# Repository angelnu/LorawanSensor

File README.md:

# STM32 Low Power LoraWan Sensors

This project provides a framework to easily build LoraWan devices. The requirements are:
- sensors that could run without replacing batteries during the life cycle of the device
- small size
- easy to build and program (need a 20-30)
- simple to create a new type: just a new file
- cost bellow 20€
- resist the outside weather with easy to 3D print cages

The sensor can work on a CR123 battery for 20 years (self-discharge of the battery being the main factor). It sends the battery voltage and (optionally) the temp of the MCU (using factory calibration).

For each new detected device it generates unique LoraWan keys and upload them to flash. This way the same firmware can be used for multiple instances of the same board.

**NOTE**: Do not put the config directory in a public repository. Instead save as extra home/private repository so you have versioning while keeping your keys private!

Download commands might be used to query or modify the configuration. See the commands section bellow.

## Bill of Materials
Devices can be built for ca 10-20€ ussing the following parts:
- STM32 MCU - any of the following:
  - STM32L412KB (3 €) - prefered: 128KB RAM for a future firmware OTA update
    - STM32L412KBT6 128K Flash,  8K RAM, LQFP-32
  - STM32L412K8 (2.5 €) - same as STM32L412KB but only 64K Flash
    - STM32L412K8T6 64K Flash,  8K RAM, LQFP-32
  - STM32L010K8 (1.5 €) - cheaper MCO+, slower, less memory, not tem and slightly higher consumption
    - STM32L412K8T6 64K Flash,  8K RAM, LQFP-32 
- RFM95W (3.5 € via Aliexpress, 3x this price if bought in Europe)
- RC123a battery and holder (2€ via Aliexpress, 2x this price if bought in Europe)
- PCB (2-5 € when ordering 12 from [Aisler](https://aisler.net) ) - see [Devices](devices) folder for the sources and the uploaded PCBs to [Aisler](https://aisler.net)
- 3D-printed boxes - see cages in [Devices](devices) folder
- some SMT components (1 €) - see schematics in [Devices](devices) folder

## Downlink commands

Downlink commands are used to query and/or modify the device settings without having to reprogram the flash. Each command uses one byte plus optional data depending on the command. The commands are implemtented in the `lorawan_process_command` at [lorawan.cpp](src/lorawan.cpp#L188)

Commands will be queued and transferred to the device after the next uplink transfer. Multiple commands can be queued but be carefull not to exceed to the watdown timeout or the device will get reset.

Commands:
- 0x00 - READ configuration
  - Description: Returns the configuration of the device. See [device_config_t](src/config.h#L23) for more details on the struct
  - Additional downlink bytes: none
  - Example output: 02 03 3C00 05 3C 6400 5802 01 0A 05 FF
- 0x01 - Reset config to the default
  - Additional downlink bytes: none
- 0x02 - Sets the configuration
  - Additional downlink bytes: config as returned by the 0x00 command
  - Example input: 02 02033C00053C64005802010A05FF
- 0x05 - Read Device UID
  - Additional downlink bytes: none
  - Output: 12 bytes with STM32 UID
- 0x06 - Read firmware GIT commit
  - Additional downlink bytes: none
  - Output: ASCII string
- 0x07 - Read firmware BUILD date
  - Additional downlink bytes: none
  - Output: ASCII string

## Firmware

This project requires [Platformio](https://platformio.org/) and the [STM32 Cube Programmer](https://www.st.com/en/development-tools/stm32cubeprog.html). Both need to be installed and available in the PATH.

Keys for each detected device will be stored under `config/devices.ini`. Before you run for the first time please create the file and include your app EUI (or modify afterwards). You can create this by registering a new app at the [TTN](https://console.thethingsnetwork.org/applications) console. The file should have:
```
[global]
appeui = <your app EUI>
```
If you run without creating the file first then the programmer will create a dummy APPEUI which you will need to modify. You can keep the config folder into its own git repository but please keep it private! On checkout you might use the [this script](checkout_keys_repo.sh) to check it out.

For programming either use the platformio UI or any of the CLI commands proposed for the device.

If you connect a serial interface while booting you should see the following:
```
Settings unchanged
DEVICE VERSION: 3
DEVICE CONFIG: 0x02033C00053C64005802010A05FF
Device UID: 0x3200230006504D3843353720
BUILD DATE: Jun 21 2020
BUILD TIME: 18:07:48
COMMIT ID: e3d1d3b5d34d39d88d90022d6fe365ebce3887b5
APPEUI: 0x.....
DEVEUI: 0x....
Starting
7579 Sending.. 18248 TX_COMPLETE
```

## Adding new devices

1. Add a section to `platformio.ini` for your device. The key part is to have a dedicated `-D SENSOR_<PCB name>_<sensor name>_<MCU name>` (such as `-D SENSOR_GENERIC_DISTANCE_SMT32`) -> this will be needed in the next step.
  - If you are just using the generic PCB then you can copy `Basic v1` and modify to your needs
  - If you are creating your own PCB based on the STM32 MCU then you can copy `Generic v1` and modify to your needs
  - If you use a different MCU then you will need to create your own target extending `base` and `base_debug`. Please notice that you will in this case have to add support for the new MCU in multiple areas of the code where the MCU is relevant: the code has been tested with STM32 (mainly) and atmega32.
2. Add a new cpp file to `src/devices/` for your new device. The namming convention is <PCB type>_<device name>_<MCU family>.cpp. If you are using a STM32 CPU you should consider copying `generic_basic_stm32.cpp` which does not depend on any external sensors to work and then add your own sensors to it. You need to make this file to only get included and compiled when `SENSOR_<PCB name>_<sensor name>_<MCU name>` is defined.
3. Add to `devices.h` a section for your device where you set your `device_config_device_t`. This struct includes what persistent settings your device needs. These settings can later be modified via a LORAWAN command.
4. Documment your device in the `devices` folder. This folder structure is:
   - _<PCB name>_
     - _cages_: instructions and files to 3D print cages for devices
     - _KiCad_: Schematics and PCBs created with KiCad
     - _pictures_: pcitures embedded in markdown readme
     - _README_: instructions, pictures and links for devices. It is structured with a chapter for each device sharing the same PCB and a subcharter for each mayor version of the device. 

## ToDos
- Firmware OTA update

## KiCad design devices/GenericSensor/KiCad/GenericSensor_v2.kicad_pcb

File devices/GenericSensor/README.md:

# Generic Sensor PCB

This device exposed all available GPIOs from the 32 pin STM32 so external sensors can be attached. Multiple use cases are listed bellow.

- 

## Versions of the PCB

### Generic Sensor v2

This verssion is backwards compatible (same posssitions for all components, even the v1 stencil might be used) but adds support for additional pull-ups or pull-downs. Check the schematic bellow to understand the options: there are two sets of solder jumpers that allow pull-up or pull-down selection. Also using 0R you can enable additional 3V and GND outputs.

- [Aisler PCB project](https://aisler.net/p/LVXPWPMZ)
- [PCB STEP model](KiCad/GenericSensor_v2.step)
- [KiCad model](KiCad\GenericSensor_v2-backups/GenericSensor_v2.kicad_pro)
- 
- 
- 

### Generic Sensor v1

This is the first version without any unneded HW. It is optimised to make it easy to esamble with only the programing pins and the battery holder not being SMD components. It does not external pull-ups so it relays into the internal ones in the MCU -> this is not the best for battery life (40 KOhms drag ca 75 uA) so v2 was develop to allow use larger (such as 10 MOhms) instead.

Since v2 is backwards compatible there is no need to use v1 anymore.

- [Aisler PCB project](https://aisler.net/p/YFVFQBHD)
- [SoilSensor.sch](KiCad/GenericSensor_v1.sch)
  - 
- [SoilSensor.kicad_pcb](KiCad/GenericSensor_v1.kicad_pcb)

## Use Cases

## Basic v1

This is mainly for debugging and as base for the other use cases. It is just the generic sensor and its embedded battery and temperature sensors.
- Sensor: none extra, just battery voltage and temperature
- Power consumption:
  - measurements: 0,4 mA, 30 ms, 1 measurement/minute
  - transmission: 120 mA, 50 ms, sending once/hour
  - iddle: 300 uA, 2 s, sending once/hour
  - deep sleep: 2 uA
  - battery: 1400 mAh
  - theoretical batery live (no auto-discharge): 39 years
- PINs: none of the external pins used
- Firmware:
  For programming either use the platformio UI or any of the following CLI commands:
  - `pio run -t upload -e generic_basic_v1` - PCB v2, STM32 L4
  - `pio run -t upload -e generic_basic_v1_debug` - PCB v2, STM32 L4, debug
- [3D Printed cage](cages):
  - None
- BUGS:
  - None so far

### Distance Sensor v1

Used to detect when a car is parked in a parking lot.

- Sensor:
  - Lidar [vl53l1x](https://www.st.com/en/imaging-and-photonics-solutions/vl53l1x.html): consumption small enough to be powered through a PIN without a mosfet - not low power enough to keep power during deep sleep. It can measure up to 4 meters.
    - Used [Melopero board](https://www.melopero.com/shop/sensori/prossimita/melopero-vl53l1x-time-of-flight-long-distance-ranging-sensor-breakout/) since it was quickly available in Amazon
    - Ordered some with cover from [China](https://de.aliexpress.com/item/4000110308676.html)
- Power consumption:
  - measurements: 1,5 mA, 120 ms, 1 measurement/minute
  - transmission: 120 mA, 50 ms, sending once/hour
  - iddle: 300 uA, 2 s, sending once/hour
  - deep sleep: 2 uA
  - battery: 1400 mAh
  - theoretical batery live (no auto-discharge): 23 years
- PINs:
  - PB7 -> vl53l1x I2C SDA
  - PB6 -> vl53l1x I2C SCL
  - PB5 -> vl53l1x VIN
  - GND -> vl53l1x GND
- Firmware:
  For programming either use the platformio UI or any of the following CLI commands:
  - `pio run -t upload -e distance_v1` - PCB v2, STM32 L4
  - `pio run -t upload -e distance_v1_debug` - PCB v2, STM32 L4, debug
- [3D Printed cage](cages/distance):
  - 
  - 
  - 
- BUGS:
  - None so far
  
### Door Sensor v1

This sensor tracks the state (open/closed) of up to 4 doors or windows. It supports two modes:
- simple: the state of the door/window is directly reported as soon as it changes
- perssistent mode (or post-mode): once the door is opened once is reported as open even if it gets closed afterwards. A second sensor is used to reset the reported door status back to closed. The reset is typically associated to a second door used to pick up the post but it could also get connected to a button that plays the same role.

- Sensor:
  - 1-8 x [Reed Contact N/O Magnetic Induction Switch](https://www.amazon.de/gp/product/B07SZDGXLC): this switch reports open so far no magnet is close. This would correspond to the door/window being open.
  - 1-8 x Circular magnet
  - 1-8 x 10 MOhms resistor
- Power consumption:
  - measurements: 1,5 mA, 40 ms, 2 measurement/day (post mode)
  - transmission: 120 mA, 50 ms, sending 2/day
  - iddle: 300 uA, 2 s, sending once/hour
  - deep sleep: 2 uA + (0.3 * number_of_sensors)
  - battery: 300 mAh
  - theoretical batery live (no auto-discharge): 23 years
- PINs (using PCB v1): each sensor needs a big (10 MOhm resistor) pull-up.
  - VCC  -> pull-up resistors
  - PB7  -> cannot be used for interrupts - conflicts with MOSI
  - PB6  -> cannot be used for interrupts - conflicts with MISO
  - PB5  -> pull-up resistor (RB5) and door 1 reed switch
  - PB4  -> pull-up resistor (RB4) and door 1 reset reed switch
  - PB3  -> pull-up resistor (RB3) and door 2 reed switch
  - PA15 -> pull-up resistor (RA15) and door 2 reset reed switch
  - PA0  -> pull-up resistor (external) and door 3 reed switch (need to uncomment in `platformio.ini`)
  - PA1  -> pull-up resistor (external) and door 3 reset reed switch (need to uncomment in `platformio.ini`)
  - PA8  -> pull-up resistor (external) and door 4 reed switch (need to uncomment in `platformio.ini`)
  - PA9  -> pull-up resistor (external) and door 4 reset reed switch (need to uncomment in `platformio.ini`)
  - GND -> reed switches
- PINs (using PCB v2) for 2 doors:
  - VCC: not used
  - RB7, RB6, RB5, RB4: 10 MOhms (0805 type)
  - RB3, RA15: 0R (0805 type)
  - Solder jumpers umodified
  - PB7  -> door 1 reed switch
  - PB6  -> reset for door 1 (or door 3) reed switch
  - PB5  -> door 2 reed switch
  - PB4  -> reset for door 2 (or door 4) reed switch
  - PB3, PA15 and both GNDs: any of the above reed switches
- Firmware:
  For programming either use the platformio UI or any of the following CLI commands:
  - `pio run -t upload -e distance_v1` - PCB v2, STM32 L4
  - `pio run -t upload -e distance_v1_debug` - PCB v2, STM32 L4, debug
- [3D Printed cage](cages/door):
  - [Fusion 360 file](https://a360.co/3GygWqv)
  - 
  - 
- BUGS:
  - None so far

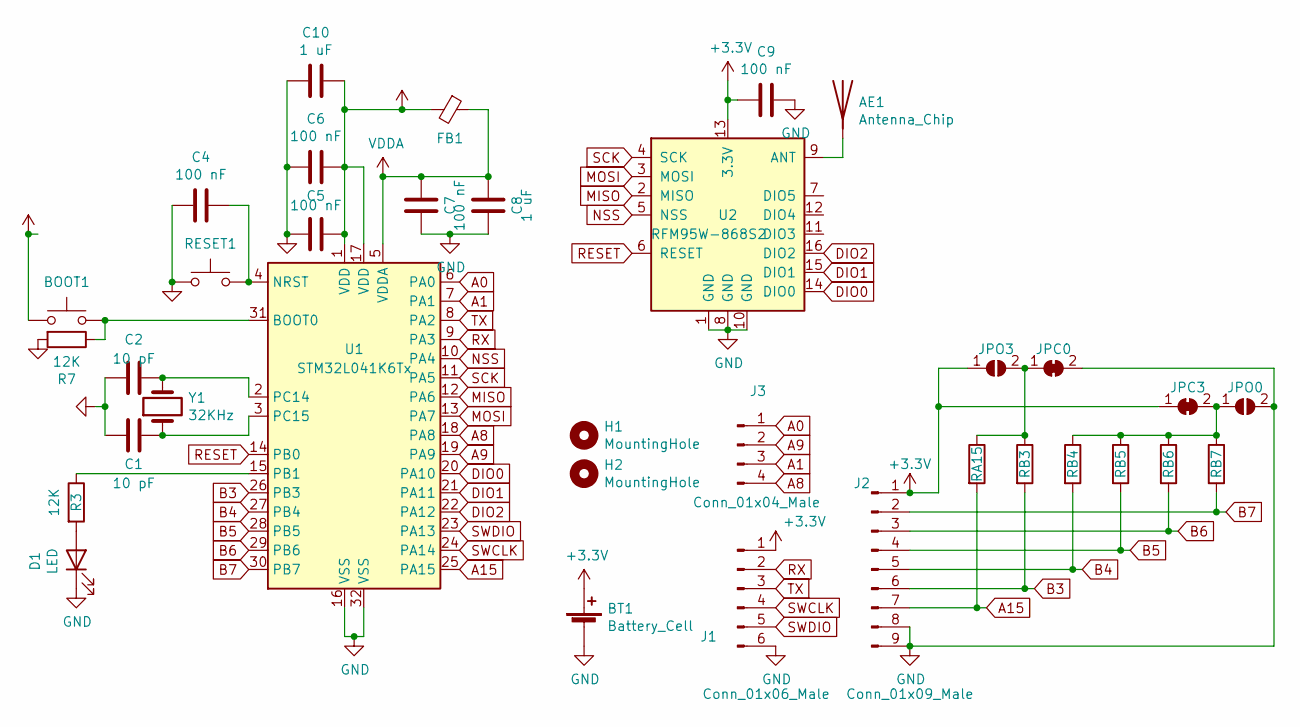
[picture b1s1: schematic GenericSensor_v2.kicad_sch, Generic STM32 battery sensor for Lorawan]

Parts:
AE1: Antenna_Chip; Texas_SWRA416_868MHz_915MHz
BOOT1: BOOT; SW_SPST_TL3342
BT1: Battery_Cell; CR123_holder
C1, C2: 10 pF; C_0805_2012Metric
C4, C5, C6, C7, C9: 100 nF; C_0805_2012Metric
C8, C10: 1 uF; C_0805_2012Metric
D1: LED; D_0805_2012Metric
FB1: Ferrite_Bead_Small; R_0805_2012Metric
H1, H2: MountingHole; MountingHole_2.2mm_M2
J1: Conn_01x06_Male; PinHeader_1x06_P2.54mm_Vertical
J2: Conn_01x09_Male; PinHeader_1x09_P2.54mm_Vertical
J3: Conn_01x04_Male; PinHeader_2x02_P2.54mm_Vertical
JPC0, JPC3: SolderJumper_2_Bridged; SolderJumper-2_P1.3mm_Bridged_Pad1.0x1.5mm
JPO0, JPO3: SolderJumper_2_Open; SolderJumper-2_P1.3mm_Open_Pad1.0x1.5mm
R3, R7: 12K; R_0805_2012Metric
RA15: PU; R_0805_2012Metric
RB3, RB4, RB5, RB6, RB7: PU; R_0805_2012Metric
RESET1: RESET; SW_SPST_TL3342
U1: STM32L041K6Tx; LQFP-32_7x7mm_P0.8mm
U2: RFM95W-868S2; HOPERF_RFM9XW_SMD
Y1: 32KHz; Crystal_SMD_3215-2Pin_3.2x1.5mm

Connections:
+3V3: BOOT1.1, BT1.1 (+), C5.1, C6.1, C9.2, C10.1, FB1.2, J1.1, J2.1, JPC3.1 (A), JPO3.1 (A), U1.1 (VDD), U1.17 (VDD), U2.13 (3.3V)
A0: J3.1, U1.6 (PA0)
A1: J3.3, U1.7 (PA1)
A8: J3.4, U1.18 (PA8)
A9: J3.2, U1.19 (PA9)
A15: J2.7, RA15.2, U1.25 (PA15)
B3: J2.6, RB3.2, U1.26 (PB3)
B4: J2.5, RB4.2, U1.27 (PB4)
B5: J2.4, RB5.2, U1.28 (PB5)
B6: J2.3, RB6.2, U1.29 (PB6)
B7: J2.2, RB7.2, U1.30 (PB7)
DIO0: U1.20 (PA10), U2.14 (DIO0)
DIO1: U1.21 (PA11), U2.15 (DIO1)
DIO2: U1.22 (PA12), U2.16 (DIO2)
GND: BT1.2 (-), C1.2, C2.2, C4.2, C5.2, C6.2, C7.1, C8.1, C9.1, C10.2, D1.1 (K), J1.6, J2.8, J2.9, JPC0.2 (B), JPO0.2 (B), R7.2, RESET1.1, U1.16 (VSS), U1.32 (VSS), U2.1 (GND), U2.8 (GND), U2.10 (GND)
MISO: U1.12 (PA6), U2.2 (MISO)
MOSI: U1.13 (PA7), U2.3 (MOSI)
NSS: U1.10 (PA4), U2.5 (NSS)
unnamed: AE1.1 (A), U2.9 (ANT)
unnamed: BOOT1.2, R7.1, U1.31 (BOOT0)
unnamed: C1.1, U1.3 (PC15), Y1.1
unnamed: C2.1, U1.2 (PC14), Y1.2
unnamed: C4.1, RESET1.2, U1.4 (NRST)
unnamed: D1.2 (A), R3.2
unnamed: JPC0.1 (A), JPO3.2 (B), RA15.1, RB3.1
unnamed: JPC3.2 (B), JPO0.1 (A), RB4.1, RB5.1, RB6.1, RB7.1
unnamed: R3.1, U1.15 (PB1)
RESET: U1.14 (PB0), U2.6 (RESET)
RX: J1.2, U1.9 (PA3)
SCK: U1.11 (PA5), U2.4 (SCK)
SWCLK: J1.4, U1.24 (PA14)
SWDIO: J1.5, U1.23 (PA13)
TX: J1.3, U1.8 (PA2)
VDDA: C7.2, C8.2, FB1.1, U1.5 (VDDA)

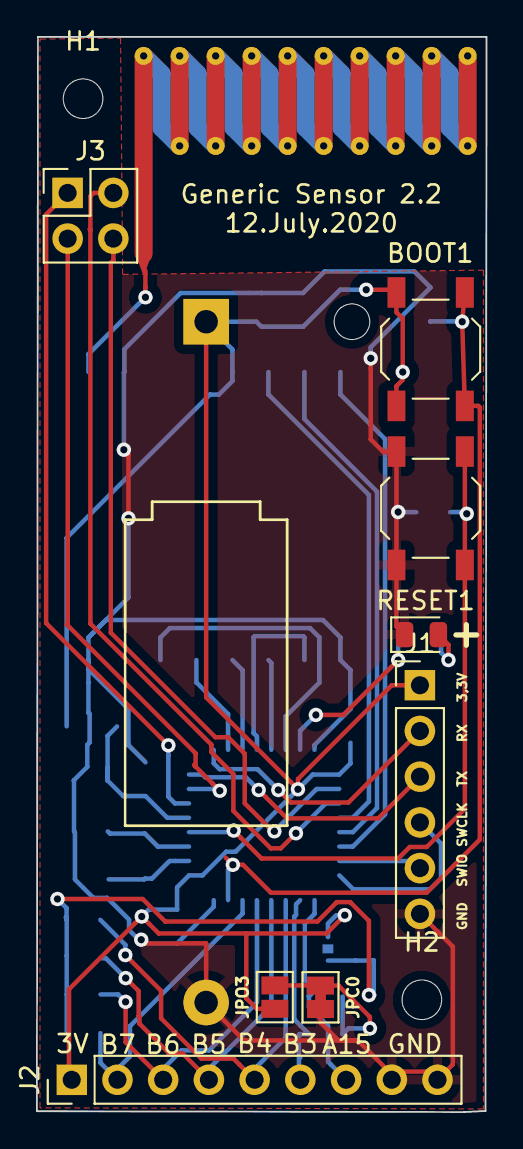
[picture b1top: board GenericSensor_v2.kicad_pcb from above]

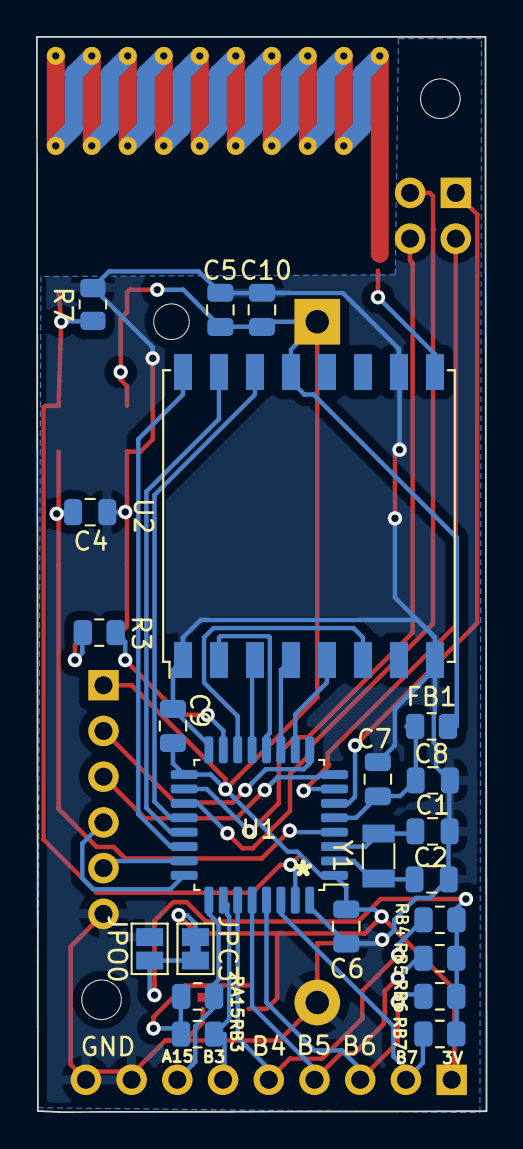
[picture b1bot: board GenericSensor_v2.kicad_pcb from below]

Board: 2 copper layers, 25.0 x 59.7 mm, 35 parts (23 on the bottom side), 34 nets.

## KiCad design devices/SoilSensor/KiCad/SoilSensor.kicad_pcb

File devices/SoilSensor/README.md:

# Capacitive Soil Sensor

This device includes a capacitive sonde in the same PCB. The resulting device can measure the soil moisture without beeing corroded nor being affected by the temperature as the resistive soil sensors.

- 

## Power cosumption

- sleep: 1.5 uA
- run: 415 uA at 4 MHz - 20 ms for measurement - 2 seconds waiting for reception
- Sending; 120 mA during 50 ms
- Sending each 60 minutes (at least moisture level changess fast - watering, raining)
- Battery: 1400 mAh
  
The above gives a theorical batery life of 47 years without auto-discharge. In reality the auto-discharge effect is expected to be the predominant one defining the live of the device to around 20 years for a good quality battery.

## References

- Moisture sensors
  - https://hackaday.io/project/161994-mesh-network-soil-moisture-sensor
  - https://flashgamer.com/blog/comments/testing-capacitive-soil-moisture-sensors
  - https://www.thethingsnetwork.org/labs/story/a-cheap-stm32-arduino-node
- Touch sensors
  - using two pins: https://github.com/PaulStoffregen/CapacitiveSensor
    - this is what it used here
  - STM32 - https://github.com/arpruss/ADCTouchSensor
    - based on https://github.com/martin2250/ADCTouch

## Versions

### Soil Sensor v2

This is the (currently) final version without any unneded HW. It is optimised to make it easy to esamble with only the programing pins and the battery holder not being SMD components.

- 

- [Aisler PCB project](https://aisler.net/p/DFIQTREA)
- [SoilSensor.sch](KiCad/SoilSensor_v2.sch)
  - 
- [SoilSensor.kicad_pcb](KiCad/SoilSensor_v2.kicad_pcb)
  - 
  - 
  - [SVG for soil sonde](pictures/soilSonde.svg)
    - edited with [Inkscape](https://inkscape.org)
    - imported to KiCad with [svg2shenzhen](https://github.com/badgeek/svg2shenzhen) plugin.
    - 
- Firmware:
  For programming either use the platformio UI or any of the following CLI commands:
  - `pio run -t upload -e soilsensor_v2_L4` - PCB v2, STM32 L4
  - `pio run -t upload -e soilsensor_v1_L4` - PCB v1, STM32 L4
  - `pio run -t upload -e soilsensor_v1_L0` - PCB v1, STM32 L0
- [3D Printed cage](cage) sealed with silicone:
  - 
  - 
- BUGS:
  - C3 (the condensator for the BOOT selector) should have been connected to GND instead of VCC to avoid starting the bootloader first time we connect the battery. Not soldering it works fine so need for a new revision.

## Soil Sensor v1

This was the first version on STM32. It has multiple debug options so more complex than needed. Battery is connected with Dupont cables.

- 

- [Aisler PCB project](https://aisler.net/p/FEKNZTQA)
- [SoilSensor.sch](KiCad/SoilSensor.sch)
  - 
- [SoilSensor.kicad_pcb](KiCad/SoilSensor.kicad_pcb)
  - 
  - 
  - 
  - [SVG for soil sonde](pictures/soilSonde.svg)
    - edited with [Inkscape](https://inkscape.org)
    - imported to KiCad with [svg2shenzhen](https://github.com/badgeek/svg2shenzhen) plugin.
    - 
- [3D Printed cage](cage) mount with battery:
  - 
  - 

- BUGS:
  - The boot input is missing a pull-up so sometimes the PCB boots into the bootloader after power-up. See [front picture](pictures/SoilSensor_v1_PCB_close_view_front.jpg) on how to manually add one.

## Soil Sensor v0

This was designed using [Fritzing](https://fab.fritzing.org/) and an Arduino pro mini. I only have a single instance running since the PCB had multiple bugs. Also the consumption was not so great since the used sensor required quite a lot of power to provide an stable read after waking up. Therefore it is not recommend to use this version.

- [Aisler PCB project](https://aisler.net/p/HJICOQLU)
- [Fritzing files](Fritzing-v0_only)
- BUGS: too many - very early prototype

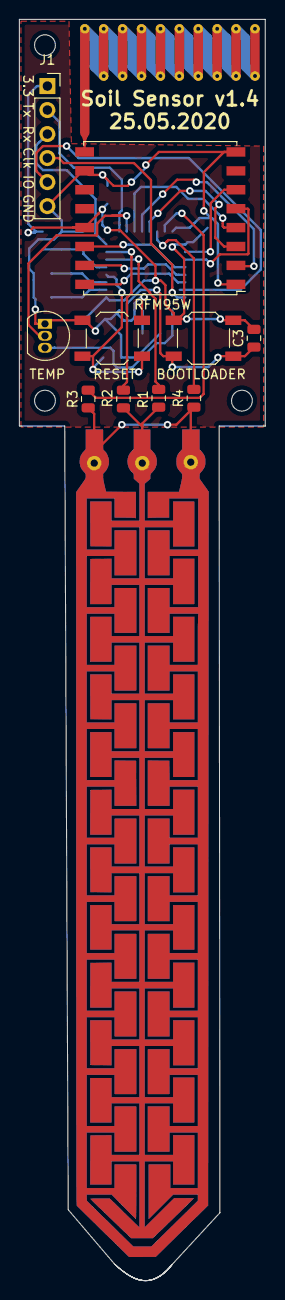
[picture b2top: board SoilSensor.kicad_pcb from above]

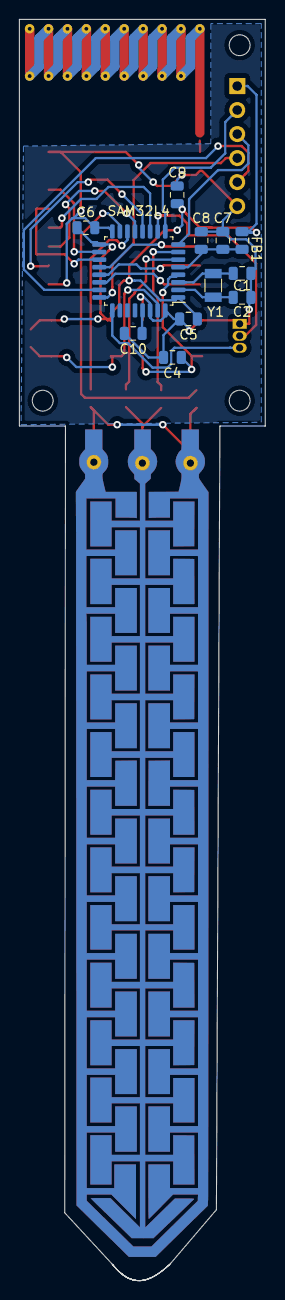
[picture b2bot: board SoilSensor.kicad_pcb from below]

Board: 2 copper layers, 26.0 x 133.4 mm, 25 parts (12 on the bottom side), 29 nets.

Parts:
 : MountingHole_2.2mm_M2
AE1: Antenna_Chip; Texas_SWRA416_868MHz_915MHz
BOOTLOADER: BOOT; SW_SPST_TL3342
C1, C2: 12,5 pF; C_0805_2012Metric
C3, C4, C5, C6, C7, C8, C9: 100 nF; C_0805_2012Metric
C10: C; C_0805_2012Metric
FB1: Ferrite_Bead_Small; R_0805_2012Metric
J1: Conn_01x06_Male; PinSocket_1x06_P2.54mm_Vertical
R1, R3: 10K; R_0805_2012Metric
R2, R4: 10M; R_0805_2012Metric
RESET: RESET; SW_SPST_TL3342
RFM95W: RFM95W-868S2; HOPERF_RFM9XW_SMD
Ref**: Val**; soilSonde
SAM32L4: STM32L041K6Tx; LQFP-32_7x7mm_P0.8mm
TEMP: DS18B20; TO-92_Inline
Y1: 32KHz; Crystal_SMD_3215-2Pin_3.2x1.5mm

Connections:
+3V3: BOOTLOADER.1, C3.2, C5.1, C6.1, C9.2, FB1.2, J1.1, RFM95W.13, SAM32L4.1, SAM32L4.17
DIO0: RFM95W.14, SAM32L4.20
DIO1: RFM95W.15, SAM32L4.21
DIO2: RFM95W.16, SAM32L4.22
GND: C1.2, C2.2, C4.2, C5.2, C6.2, C7.1, C8.1, C9.1, C10.2, J1.6, RESET.1, RFM95W.1, RFM95W.8, RFM95W.10, SAM32L4.16, SAM32L4.30, SAM32L4.32, TEMP.1
MISO: RFM95W.2, SAM32L4.12
MOSI: RFM95W.3, SAM32L4.13
NSS: RFM95W.5, SAM32L4.19
unnamed: AE1.1, RFM95W.9
unnamed: C1.1, SAM32L4.3, Y1.1
unnamed: C2.1, SAM32L4.2, Y1.2
unnamed: BOOTLOADER.2, C3.1, SAM32L4.31
unnamed: C4.1, RESET.2, SAM32L4.4
unnamed: C10.1, SAM32L4.29
unnamed: R1.1, SAM32L4.6
unnamed: R2.1, SAM32L4.7
unnamed: R3.2, SAM32L4.15
unnamed: R4.2, SAM32L4.14
unnamed: SAM32L4.10, TEMP.2
unnamed: SAM32L4.25, TEMP.3
RESET: RFM95W.6, SAM32L4.18
RX: J1.3, SAM32L4.8
SCK: RFM95W.4, SAM32L4.11
SONDE: R1.2, R2.2, Ref**.2
SONDE_SHIELD: R3.1, R4.1, Ref**.1
SWCLK: J1.4, SAM32L4.24
SWDIO: J1.5, SAM32L4.23
TX: J1.2, SAM32L4.9
VDDA: C7.2, C8.2, FB1.1, SAM32L4.5

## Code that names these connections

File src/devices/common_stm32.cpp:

#if defined(ARDUINO_ARCH_STM32)

#include "common_stm32.h"
#include "sensor.h"

#define ADC_RANGE (1<<ADC_RESOLUTION)

// Average
uint32_t averageAnalogInput(uint32_t pin, uint8_t measurements) {
  uint32_t total = 0;
  for (uint8_t i=0; i<measurements; i++){
    total += analogRead(pin);
  }
  return total / measurements;

}

// VREF

//See https://github.com/stm32duino/Arduino_Core_STM32/pull/539
const uint16_t* const ADC_VREFINT_3V0_30C =  reinterpret_cast<uint16_t*>(ADC_VREFINT_3V0_30C_ADDR);
const uint32_t CALIBRATION_REFERENCE_VOLTAGE = 3000;
const float VREFINT = CALIBRATION_REFERENCE_VOLTAGE * (*ADC_VREFINT_3V0_30C) / ADC_RANGE;

uint32_t readVref()
{
  return (VREFINT * ADC_RANGE / averageAnalogInput(AVREF, device_config.measure_average)); // ADC sample to mV
}


// TEMPERATURE
#ifdef ADC_TEMP_3V0_30C_ADDR
    // see datasheet for position of the calibration values, this is for STM32L4xx
    const uint16_t* const ADC_TEMP_3V0_30C =  reinterpret_cast<uint16_t*>(ADC_TEMP_3V0_30C_ADDR);
    const uint16_t* const ADC_TEMP_3V0_130C =  reinterpret_cast<uint16_t*>(ADC_TEMP_3V0_130C_ADDR);


    float readTempSensor(int32_t VRef)
    {
    // scale constants to current reference voltage
    float adcCalTemp30C = static_cast<float>(*ADC_TEMP_3V0_30C);
    float adcCalTemp130C = static_cast<float>(*ADC_TEMP_3V0_130C);

    //Read and convert to calibration value
    float adcTempValue = 1.0 * averageAnalogInput(ATEMP, device_config.measure_average) * VRef / CALIBRATION_REFERENCE_VOLTAGE;

    return (adcTempValue - adcCalTemp30C)/(adcCalTemp130C - adcCalTemp30C) * (130.0 - 30.0) + 30.0;
    }
#else
  float readTempSensor(int32_t VRef) {return 0;}
#endif


void allInput()
{
  pinMode(PA0, INPUT_PULLDOWN);
  pinMode(PA1, INPUT_PULLDOWN);
  //Serial port
  //pinMode(PA2, INPUT_PULLDOWN);
  //pinMode(PA3, INPUT_PULLDOWN);
  pinMode(PA4, INPUT_PULLDOWN);
  pinMode(PA5, INPUT_PULLDOWN);
  pinMode(PA6, INPUT_PULLDOWN);
  pinMode(PA7, INPUT_PULLDOWN);
  pinMode(PA8, INPUT_PULLDOWN);
  pinMode(PA9, INPUT_PULLDOWN);
  pinMode(PA10, INPUT_PULLDOWN);
  
  pinMode(PA11, INPUT_PULLDOWN);
  pinMode(PA12, INPUT_PULLDOWN);
  //WSI port
  //pinMode(PA13, INPUT_PULLDOWN);
  //pinMode(PA14, INPUT_PULLDOWN);
  pinMode(PA15, INPUT_PULLDOWN);

  pinMode(PB0, INPUT_PULLDOWN);
  pinMode(PB1, INPUT_PULLDOWN);
  pinMode(PB3, INPUT_PULLDOWN);
  pinMode(PB4, INPUT_PULLDOWN);
  pinMode(PB5, INPUT_PULLDOWN);
  pinMode(PB6, INPUT_PULLDOWN);
  pinMode(PB7, INPUT_PULLDOWN);
}

#endif

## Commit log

2020-06-21 Initial public release
2020-06-21 Add command documentation
2020-06-21 Add detect flash memory and program optionbytes
2020-06-21 delta since last transmission, not since last measurement
2020-06-21 Fix name in devices.ini
2020-06-21 Update version
2020-06-21 Add support for EEPROM for lorawan keys
2020-06-21 Remove soilsensor_v2_L4s - memory autodetected now
2020-06-22 3D-printed box files for sensor cages
2020-06-23 Correct setting optionbytes
2020-06-23 Change default to v2
2020-06-23 Documment KiCad
2020-06-23 Add aisler links
2020-06-23 Newest up
2020-06-27 Fix setOptionBytes
2020-06-28 rework for multi device
2020-06-28 default error
2020-06-28 Rework documentantion
2020-06-28 fix links
2020-06-28 fix picture links
2020-06-29 Create LICENSE
2020-07-04 Reset config when switching from debug to reset
2020-07-04 Working distance sensor
2020-07-04 Make version device specific
2020-07-04 Do not send due to extended parms
2020-07-04 Small fixes for distance
2020-07-04 Add basic sensor
2020-07-04 Add sleep after recovering from watchdog
2020-07-05 Fix dup channel
2020-07-05 Fix lib depss
2020-07-05 WIP for new subsecond sleep
2020-07-05 Small revision -> 2.2
2020-07-11 Document howto add new devices
2020-07-11 Use stm32duino master
2020-07-11 Support to skip next sleep
2020-07-11 Add door sensor
2020-07-12 Version 7 - door sensor tested
2020-07-12 Add PCB v2
2020-07-12 Add pins for v2
2020-07-14 Added 3D piece files and pictures
    Added 3D piece files for Distance and door sensor.
2020-07-14 Rename picture file
2020-07-18 fix link
2020-07-18 Fix channel dup
2020-07-26 WIP for tracker
2020-08-19 Adding tracker - before class rework
2020-08-25 Resstruct in senssor classes
2020-08-29 Add tracker pictures
    Added pictures to tracker project.
2020-08-29 rename tracker pictures
2020-08-29 rename traker picture
2020-08-29 rename pictures
2020-08-29 % not calculated correctly
2020-08-29 wait for satelite in release mode only
2020-08-29 Do not count skipped measurements in fast mode
2020-08-29 reset did not work
2020-08-30 switch to use C lib from STM
2020-08-30 make enum for channels
2020-08-31 do no pull dow SDO
2020-08-31 Use pull-down in sleep
2020-08-31 use LP while sleeping
2020-08-31 disable stlink in release
2020-08-31 fix fast sleep time
2020-08-31 give more time for warm start
2020-08-31 remove stlink in sleep in release mode
2020-08-31 simplify loop
2020-08-31 if interrupt comes CPU wakes up even in disabled
2020-08-31 Reset filter reference on each measurement
2020-08-31 Change conditionss
2020-08-31 always send when moving
2020-09-01 init debug variable
2020-09-01 download lib automatically
2020-09-03 remove return
2020-09-03 use long range
2020-09-07 detect when waking up from int
2020-09-07 Solve conflict with MISO/MOSI
2021-01-16 Support latest platformio
2021-01-16 fix include case
2021-01-16 Fix tracker build
2021-01-16 Fix for tracker
2021-01-16 CI test
2021-01-16 checkout submodules
2021-01-16 Fix case for Vector include
2021-01-16 fix CI
2021-01-18 support for Windows
2021-06-06 instructions for git config
2022-01-16 refresh to latest libraries
2022-01-17 Add renovate.json
2022-01-17 Add more 3D models
2022-01-18 add pictures
2022-02-28 Update actions/setup-python action to v3
2022-03-01 Update actions/checkout action to v3
2022-03-06 Remove platform that does not longer fit
2022-03-21 Update actions/cache action to v3
2022-06-18 Update actions/setup-python action to v4
2022-06-19 Create .python-version
2022-06-19 Update dependency python to v3
2022-10-16 add default renovate
2022-10-23 fix build errors due to old versions
2022-11-05 update bot email
2022-12-26 retry begin
2023-04-10 log what sensor triggered the transmission
2024-01-21 support remote
2024-01-21 a lot of debug
